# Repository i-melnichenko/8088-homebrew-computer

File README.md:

# 8088 Homebrew Computer

An open-source modular computer built around the Intel 8088 CPU, using
through-hole DIP components and a custom expansion architecture. Development
proceeds incrementally from a minimal working system toward additional hardware
and software capabilities.

## Mainboard Rev. 2.0

| Front | Left-side assembly view |
| --- | --- |
|  |  |

## Firmware and host tools

The repository includes a [32 KiB ROM BIOS](firmware/8088-mainboard/README.md),
[boardctl](tools/boardctl/README.md), and two supported operating systems:

| Operating system | Build from the repository root | Disk image |
| --- | --- | --- |
| [HOME8088 OS](firmware/8088-mainboard/os/home8088/README.md) | `make -C firmware/8088-mainboard os` | `home8088.img` |
| [Microsoft MS-DOS 2.0](firmware/8088-mainboard/os/msdos/README.md) | `make -C firmware/8088-mainboard msdos` | `msdos20.img` |

BIOS performs POST, offers a 20×4 LCD menu for boot/diagnostics/info, and exposes
PC-style hardware services. Both operating systems boot from FAT12
floppy images served by boardctl over UART. Images are writable by default.
Generated base images live in `firmware/8088-mainboard/build/`; keep persistent
DOS files and saves in working copies under `firmware/8088-mainboard/disks/`.

For example, build and boot HOME8088 OS from the repository root:

```sh
make -C firmware/8088-mainboard bios os BIOS_VERSION=dev-disk
go -C tools/boardctl build -o boardctl ./cmd
tools/boardctl/boardctl -port /dev/cu.usbserial-XXXX info
tools/boardctl/boardctl -port /dev/cu.usbserial-XXXX terminal \
  --disk firmware/8088-mainboard/build/home8088.img --boot
```

Install the built BIOS before booting the OS. HOME8088 applications run with
RUN CITY, RUN TIMER or RUN TERMINAL; MS-DOS starts DOS programs by filename.
BIOS/boardctl do not manage application uploads or resident slots. Normal host operations require
[UART protocol 2.0](docs/uart-protocol.md); EEPROM operations negotiate the
installed upgrade transport separately so an older BIOS can still be updated.
The independent updater lives in `firmware/8088-mainboard/bios/programs/flasher`.

Rev. 2 uses on-board UART at 3F8..3FF, 9600 8N1, optional PIC/PIT, and an optional
20×4 LCD with JP1 bridged (80/81 ports). POST detects installed SRAM chips across
00000..9FFFF; the monitor/updater need one working chip anywhere. OS boot requires
RAM0 and a verified timer, reserving the upper 32 KiB of contiguous RAM for BIOS.
The PC timer runs at about 18.2065 Hz. Both operating systems use BIOS disk,
keyboard, console and time services.

Microsoft MS-DOS uses the original, unmodified Microsoft 2.00 kernel and COMMAND
2.02 with the board's OEM I/O layer. The image includes DEBUG and a DOS example;
`make -C firmware/8088-mainboard msdos-zork` adds Zork I in `msdos20-zork.img`.
Prepare a working copy after building DOS, then boot it through the same BIOS
and boardctl (from the repository root):

```sh
mkdir -p firmware/8088-mainboard/disks
cp -n firmware/8088-mainboard/build/msdos20.img firmware/8088-mainboard/disks/msdos20.img
tools/boardctl/boardctl -port /dev/cu.usbserial-XXXX terminal \
  --disk firmware/8088-mainboard/disks/msdos20.img --boot
```

The supported DOS configuration uses the UART console and writable disk images.
Add `--disk-readonly` to protect an image from guest writes.
See the [DOS guide](firmware/8088-mainboard/os/msdos/README.md) for tested programs
and current hardware and storage limits.

## Architecture

The mainboard is built around an Intel 8088 in minimum mode. It exposes a
20-bit address bus (`A0…A19`) and an 8-bit data bus (`D0…D7`); two 74LS373
latches demultiplex `AD0…AD7`, and a 74LS245 buffers the data bus.

## Memory map

| Address range | Function |
| --- | --- |
| `00000h–9FFFFh` | 640 KiB SRAM (five 128 KiB banks) |
| `A0000h–BFFFFh` | `EXP_MEM_CS5#` expansion-memory window, including the conventional `B8000h` video-memory area; available on both Exp0 and Exp1 |
| `C0000h–DFFFFh` | `EXP_MEM_CS6#` expansion-memory / option-ROM window; available on both Exp0 and Exp1 |
| `E0000h–FFFFFh` | 28C256 boot ROM (32 KiB mirrored in the window) |

## I/O map

| Device | Primary ports | Notes |
| --- | --- | --- |
| 8259A PIC | `20h`, `21h` | Interrupt controller |
| 8254 PIT | `40h–43h` | System timer |
| GM16C550 UART | `3F8h–3FFh` | COM1-compatible; mirrored because decoding is partial |
| `EXP_IO_CS4#` | `80h–9Fh` | Expansion I/O window; available on both Exp0 and Exp1 |
| `EXP_IO_CS5#` | `A0h–BFh` | Expansion I/O window; available on both Exp0 and Exp1 |
| `EXP_IO_CS6#` | `C0h–DFh` | Expansion I/O window; available on both Exp0 and Exp1 |

## UART console

The GM16C550 UART provides a COM1-compatible console at `3F8h–3FFh`. Its
1.8432 MHz crystal supports common serial rates; the current BIOS and
`boardctl` use 9600 8N1.

`J9` is a 3-pin TTL UART header (`GND`, `TXD`, `RXD`). To connect the computer
to a USB host, use an external **CP2102 USB-to-TTL adapter**: connect ground
and cross `TXD` with `RXD`. The CP2102 is powered by USB; do not connect its
power pin to the mainboard through `J9`. Verify that the selected CP2102 board
accepts the mainboard's 5 V TTL `TXD` level. This is not an RS-232 interface;
use a MAX232-compatible level converter before connecting an RS-232 port.

## Interrupts and timer

The 8259A PIC operates as a single 8086/8088-mode master and drives the
processor `INTR` input. The 8254 PIT provides the system tick: its channel 0
receives a 1.1931817 MHz clock from a 74LS74 divider and, when programmed with
a divisor of 65,536 in mode 2, produces an 18.2065 Hz interrupt on `IR0`.

| PIC input | PCB connection |
| --- | --- |
| `IR0` | `PIT_IRQ` from the 8254 system timer |
| `IR1` | `EXP_IRQ1` expansion line |
| `IR2` | `EXP_IRQ2` expansion line |
| `IR3` | `EXP_IRQ3` expansion line |
| `IR4` | `UART_IRQ` from the GM16C550 UART |
| `IR5` | `EXP_IRQ5` expansion line |
| `IR6` | `EXP_IRQ6` expansion line |
| `IR7` | `EXP_IRQ7` expansion line |

Each PIC request input has a 10 kΩ pull-down, keeping it inactive when no
device drives the line. Firmware must initialize the PIC and PIT before
enabling interrupts.

## Expansion modules

The mechanical and electrical contract for daughterboards is defined in the
[Expansion Module Standard Rev.2](docs/expansion-module-standard.md).

| Module | Purpose | Documentation |
| --- | --- | --- |
| Display Module | HD44780-compatible character LCD interface | [Configuration and BOM](docs/display-module.md) |
| Smart I/O Module | ESP32-based smart I/O, TFT, and SD interface | [Configuration and BOM](docs/smart-io-module.md) |

## Bill of materials

The table below is derived from [`hardware/kicad`](hardware/kicad) for Rev. 2.0.
It includes both through-hole and SMD components.

| Designators | Qty. | Part / value | Footprint / notes |
| --- | ---: | --- | --- |
| U1 | 1 | Intel 8088, minimum mode | DIP-40, 15.24 mm socket footprint |
| U2, U3 | 2 | 74LS373 | DIP-20, 7.62 mm socket footprint |
| U4 | 1 | 74LS245 | DIP-20, 7.62 mm socket footprint |
| U5 | 1 | 8284 clock generator / driver | DIP-18, 7.62 mm socket footprint |
| U6, U7 | 2 | 74LS138 | DIP-16, 7.62 mm socket footprint |
| U8 | 1 | 28C256 EEPROM | DIP-28 socket footprint; 3M 228-1277-00-0602J |
| U9–U13 | 5 | AS6C1008-55PCN SRAM | DIP-32, 15.24 mm socket footprint |
| U14 | 1 | GM16C550 UART | DIP-40, 15.24 mm socket footprint |
| U15 | 1 | 8259A-2 programmable interrupt controller | DIP-28, 15.24 mm socket footprint |
| U16 | 1 | 8254 programmable interval timer | DIP-24, 15.24 mm socket footprint |
| U17 | 1 | 74LS74 | DIP-14, 7.62 mm socket footprint |
| Q1 | 1 | NDP6020P P-channel MOSFET | TO-220-3, horizontal tab-down |
| Y1 | 1 | 14.31818 MHz crystal | HC-49/U, vertical |
| Y2 | 1 | 1.8432 MHz crystal | HC-49/U, vertical |
| R1–R3, R5–R7, R9–R10, R12, R15–R18, R21–R28 | 21 | 10 kΩ | 0805 SMD |
| R8, R19 | 2 | 1 kΩ | 0805 SMD |
| R11, R20 | 2 | 2 kΩ | 0805 SMD |
| R4 | 1 | 680 Ω | 0805 SMD |
| R13 | 1 | 1 MΩ | 0805 SMD |
| R14 | 1 | 1.5 kΩ | 0805 SMD |
| R29–R44 | 16 | 33 Ω | 0805 SMD; series isolation of the `D0…D7` branches for Exp0 and Exp1 |
| C1–C4, C6–C14, C18–C21 | 17 | 100 nF ceramic | 0805 SMD |
| C5 | 1 | 10 µF electrolytic | Radial, 1.50 mm pitch |
| C15 | 1 | 220 µF electrolytic | Radial, 2.00 mm pitch |
| C16 | 1 | 22 pF ceramic | 0805 SMD |
| C17 | 1 | 47 pF ceramic | 0805 SMD |
| D1 | 1 | Reset LED | 0805 SMD |
| D2 | 1 | Power LED | 0805 SMD |
| SW1 | 1 | 3-position DIP switch | SPST ×3, 2.54 mm pitch |
| SW2 | 1 | Reset pushbutton | 6 mm THT tactile switch |
| J1 | 1 | 10-pin connector | 1×10 pin header, 2.54 mm pitch |
| J2 | 1 | External reset connector | 1×2 pin header, 2.54 mm pitch |
| J3 | 1 | External clock connector | 1×2 pin header, 2.54 mm pitch |
| J4, J6 | 2 | Expansion connectors (Exp0-A, Exp1-A) | 2×20 pin socket, 2.54 mm pitch |
| J5, J7 | 2 | Expansion connectors (Exp0-B, Exp1-B) | 2×10 pin socket, 2.54 mm pitch |
| J8 | 1 | 5 V power input | 2-pin Phoenix MKDS-1,5, 5.08 mm pitch |
| J9 | 1 | CP2102 module connector | 1×3 pin header, 2.54 mm pitch |
| J10, J11 | 2 | 4-pin auxiliary connectors | 1×4 pin header, 2.54 mm pitch |

For ICs, sockets are recommended; the PCB footprints already provide for them.

## Links

- [DIY EEPROM Programmer](https://github.com/erikvanzijst/eeprom)

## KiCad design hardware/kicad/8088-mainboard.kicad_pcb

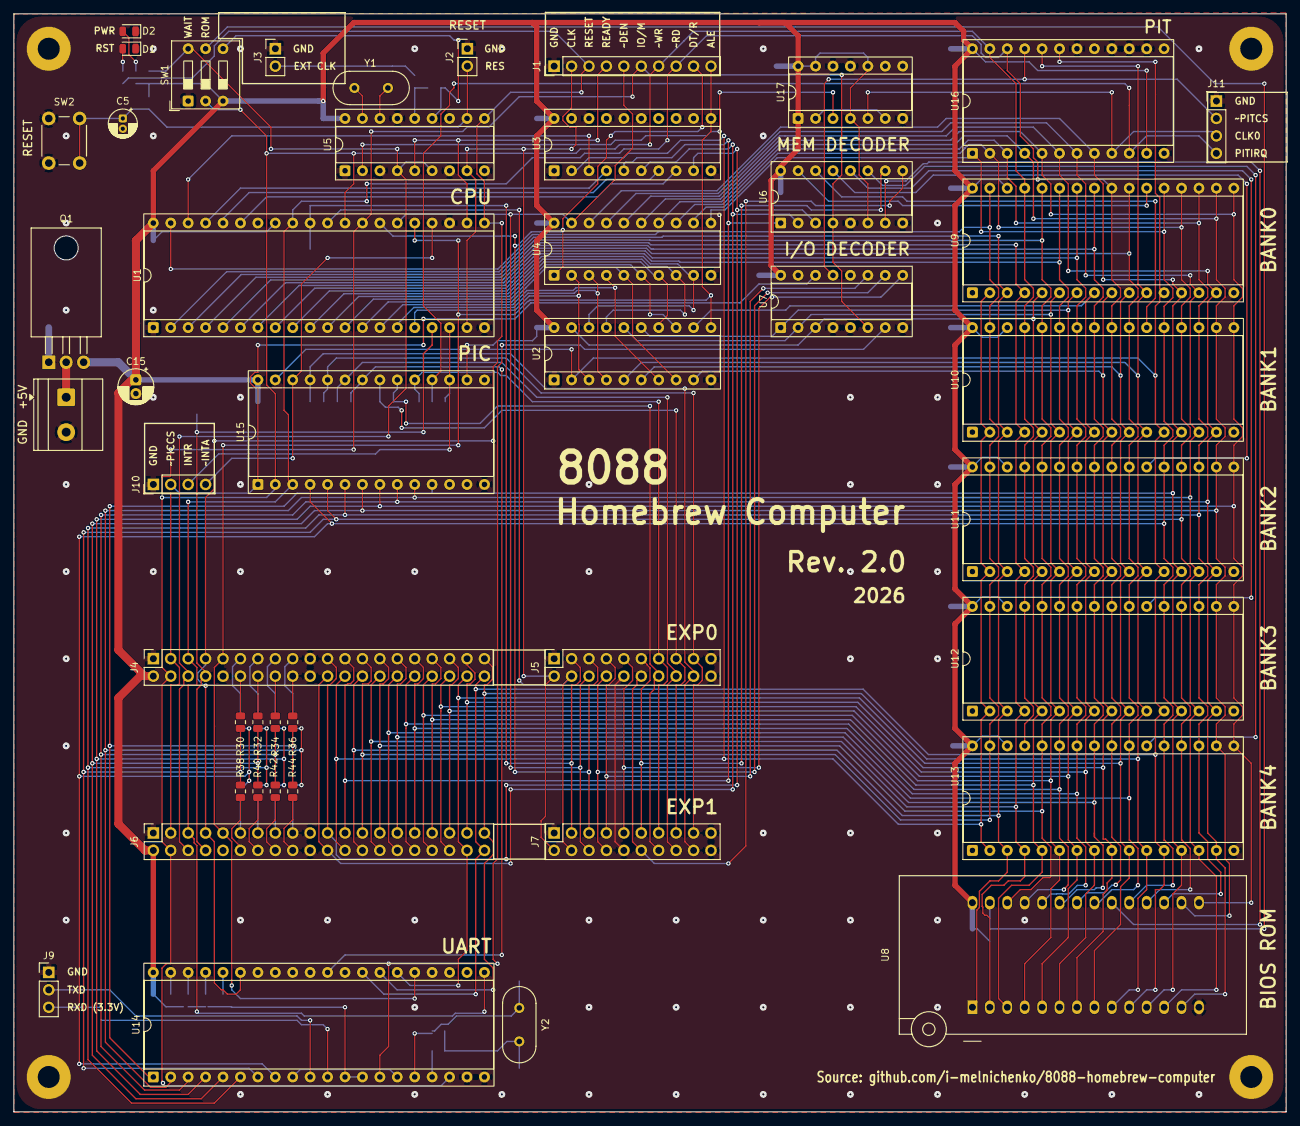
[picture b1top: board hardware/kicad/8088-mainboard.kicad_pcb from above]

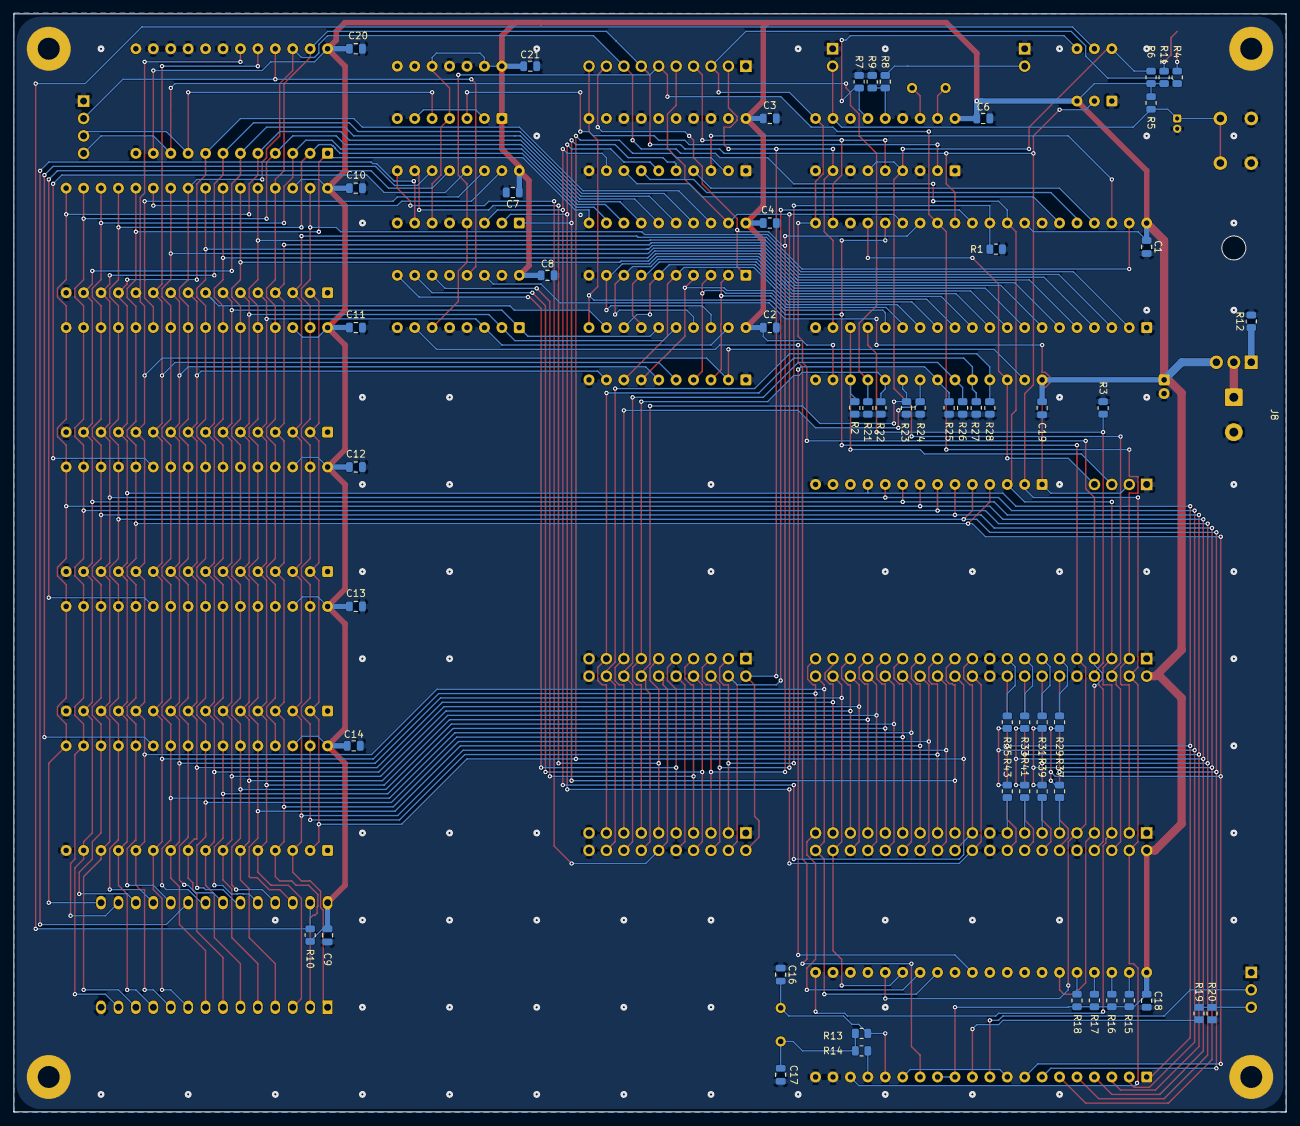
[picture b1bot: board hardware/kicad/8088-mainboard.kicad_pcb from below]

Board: 2 copper layers, 185.4 x 160.0 mm, 104 parts (55 on the bottom side), 120 nets.

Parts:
C1, C2, C3, C4, C7, C8, C9, C10, C11, C12, C13, C14, C18, C19, C20, C21: 100nF; C_0805_2012Metric
C5: 10 uF; CP_Radial_D4.0mm_P1.50mm
C6: 100 nF; C_0805_2012Metric
C15: 220 uF; CP_Radial_D5.0mm_P2.00mm
C16: 22pF; C_0805_2012Metric
C17: 47pF; C_0805_2012Metric
D1: RST LED; LED_0805_2012Metric
D2: PWR LED; LED_0805_2012Metric
H1, H2, H3, H4: MountingHole_Pad; MountingHole_3.2mm_M3_Pad
J1: Conn_01x10; PinHeader_1x10_P2.54mm_Vertical
J2: Ext Res; PinHeader_1x02_P2.54mm_Vertical
J3: Ext CLK; PinHeader_1x02_P2.54mm_Vertical
J4: EXP_0_A; PinSocket_2x20_P2.54mm_Vertical
J5: EXP_0_B; PinSocket_2x10_P2.54mm_Vertical
J6: EXP_1_A; PinSocket_2x20_P2.54mm_Vertical
J7: EXP_1_B; PinSocket_2x10_P2.54mm_Vertical
J8: POWER 5v; TerminalBlock_Phoenix_MKDS-1,5-2-5.08_1x02_P5.08mm_Horizont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
J9: CP2102 Module; PinHeader_1x03_P2.54mm_Vertical
J10, J11: Conn_01x04; PinHeader_1x04_P2.54mm_Vertical
Q1: NDP6020P; TO-220-3_Horizontal_TabDown
R1, R2, R3, R5, R6, R7, R9, R10, R12, R15, R16, R17, R18, R21, R22, R23, R24, R25, R26, R27, R28: 10k; R_0805_2012Metric
R4: 680; R_0805_2012Metric
R8, R19: 1k; R_0805_2012Metric
R11: 2k; R_0805_2012Metric
R13: 1M; R_0805_2012Metric
R14: 1.5k; R_0805_2012Metric
R20: 2K; R_0805_2012Metric
R29, R30, R31, R32, R33, R34, R35, R36, R37, R38, R39, R40, R41, R42, R43, R44: 33; R_0805_2012Metric
SW1: SW_DIP_x03; SW_DIP_SPSTx03_Slide_9.78x9.8mm_W7.62mm_P2.54mm
SW2: Reset; SW_PUSH_6mm
U1: 8088_Min_Mode; DIP-40_W15.24mm_Socket
U2, U3: 74LS373; DIP-20_W7.62mm_Socket
U4: 74LS245; DIP-20_W7.62mm_Socket
U5: 8284; DIP-18_W7.62mm_Socket
U6, U7: 74LS138; DIP-16_W7.62mm_Socket
U8: 28C256; DIP_Socket-28_W11.9mm_W12.7mm_W15.24mm_W17.78mm_W18.5mm_3M_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
U9, U10, U11, U12, U13: AS6C1008-55PCN; DIP-32_W15.24mm_Socket
U14: GM16C550; DIP-40_W15.24mm_Socket
U15: 8259A-2; DIP-28_W15.24mm_Socket
U16: 8254; DIP-24_W15.24mm_Socket
U17: 74LS74; DIP-14_W7.62mm_Socket
Y1: 14.31818 MHz; Crystal_HC49-U_Vertical
Y2: 1.8432 MHz; Crystal_HC49-U_Vertical

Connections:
/A0: J4.40, J6.40, U2.2 (O0), U8.10 (A0), U9.12 (A0), U10.12 (A0), U11.12 (A0), U12.12 (A0), U13.12 (A0), U14.28 (A0), U15.27 (A0), U16.19 (A0)
/A1: J4.39, J6.39, U2.5 (O1), U8.9 (A1), U9.11 (A1), U10.11 (A1), U11.11 (A1), U12.11 (A1), U13.11 (A1), U14.27 (A1), U16.20 (A1)
/A2: J4.38, J6.38, U2.6 (O2), U8.8 (A2), U9.10 (A2), U10.10 (A2), U11.10 (A2), U12.10 (A2), U13.10 (A2), U14.26 (A2)
/A3: J4.37, J6.37, U2.9 (O3), U8.7 (A3), U9.9 (A3), U10.9 (A3), U11.9 (A3), U12.9 (A3), U13.9 (A3)
/A4: J4.36, J6.36, U2.12 (O4), U8.6 (A4), U9.8 (A4), U10.8 (A4), U11.8 (A4), U12.8 (A4), U13.8 (A4)
/A5: J4.35, J6.35, U2.15 (O5), U7.1 (A0), U8.5 (A5), U9.7 (A5), U10.7 (A5), U11.7 (A5), U12.7 (A5), U13.7 (A5)
/A6: J4.34, J6.34, U2.16 (O6), U7.2 (A1), U8.4 (A6), U9.6 (A6), U10.6 (A6), U11.6 (A6), U12.6 (A6), U13.6 (A6)
/A7: J4.33, J6.33, U2.19 (O7), U7.3 (A2), U8.3 (A7), U9.5 (A7), U10.5 (A7), U11.5 (A7), U12.5 (A7), U13.5 (A7)
/A8: J4.32, J6.32, U1.8 (A8), U8.25 (A8), U9.27 (A8), U10.27 (A8), U11.27 (A8), U12.27 (A8), U13.27 (A8)
/A9: J4.31, J6.31, U1.7 (A9), U8.24 (A9), U9.26 (A9), U10.26 (A9), U11.26 (A9), U12.26 (A9), U13.26 (A9)
/A10: J4.30, J6.30, U1.6 (A10), U8.21 (A10), U9.23 (A10), U10.23 (A10), U11.23 (A10), U12.23 (A10), U13.23 (A10)
/A11: J4.29, J6.29, U1.5 (A11), U8.23 (A11), U9.25 (A11), U10.25 (A11), U11.25 (A11), U12.25 (A11), U13.25 (A11)
/A12: J4.28, J6.28, U1.4 (A12), U8.2 (A12), U9.4 (A12), U10.4 (A12), U11.4 (A12), U12.4 (A12), U13.4 (A12)
/A13: J4.27, J6.27, U1.3 (A13), U8.26 (A13), U9.28 (A13), U10.28 (A13), U11.28 (A13), U12.28 (A13), U13.28 (A13)
/A14: J4.26, J6.26, U1.2 (A14), U8.1 (A14), U9.3 (A14), U10.3 (A14), U11.3 (A14), U12.3 (A14), U13.3 (A14)
/A15: J4.25, J6.25, U1.39 (A15), U9.31 (A15), U10.31 (A15), U11.31 (A15), U12.31 (A15), U13.31 (A15)
/A16: J4.24, J6.24, U3.2 (O0), U9.2 (A16), U10.2 (A16), U11.2 (A16), U12.2 (A16), U13.2 (A16)
/A17: J4.23, J6.23, U3.5 (O1), U6.1 (A0)
/A18: J4.22, J6.22, U3.6 (O2), U6.2 (A1)
/A19: J4.21, J6.21, U3.9 (O3), U6.3 (A2)
/ALE: J1.10, J4.9, J6.9, U1.25 (ALE), U2.11 (LE), U3.11 (LE), U14.25 (~ADS)
/CLK: J1.2, J5.2, J7.2, U1.19 (CLK), U5.8 (CLK)
/CLOCK/RES: C5.1, J2.2, R5.2, SW2.1, U5.11 (~RES)
/CLOCK_EFI_SW: R7.1, SW1.4, U5.13 (F/~C)
/CPU/AD0: U1.16 (AD0), U2.3 (D0), U4.2 (A0)
/CPU/AD1: U1.15 (AD1), U2.4 (D1), U4.3 (A1)
/CPU/AD2: U1.14 (AD2), U2.7 (D2), U4.4 (A2)
/CPU/AD3: U1.13 (AD3), U2.8 (D3), U4.5 (A3)
/CPU/AD4: U1.12 (AD4), U2.13 (D4), U4.6 (A4)
/CPU/AD5: U1.11 (AD5), U2.14 (D5), U4.7 (A5)
/CPU/AD6: U1.10 (AD6), U2.17 (D6), U4.8 (A6)
/CPU/AD7: U1.9 (AD7), U2.18 (D7), U4.9 (A7)
/CPU/AD16: U1.38 (A16/S3), U3.3 (D0)
/CPU/AD17: U1.37 (A17/S4), U3.4 (D1)
/CPU/AD18: U1.36 (A18/S5), U3.7 (D2)
/CPU/AD19: U1.35 (A19/S6), U3.8 (D3)
/D0: R36.2, R44.2, U4.18 (B0), U8.11 (D0), U9.13 (DQ0), U10.13 (DQ0), U11.13 (DQ0), U12.13 (DQ0), U13.13 (DQ0), U14.1 (D0), U15.11 (D0), U16.8 (D0)
/D1: R35.2, R43.2, U4.17 (B1), U8.12 (D1), U9.14 (DQ1), U10.14 (DQ1), U11.14 (DQ1), U12.14 (DQ1), U13.14 (DQ1), U14.2 (D1), U15.10 (D1), U16.7 (D1)
/D2: R34.2, R42.2, U4.16 (B2), U8.13 (D2), U9.15 (DQ2), U10.15 (DQ2), U11.15 (DQ2), U12.15 (DQ2), U13.15 (DQ2), U14.3 (D2), U15.9 (D2), U16.6 (D2)
/D3: R33.2, R41.2, U4.15 (B3), U8.15 (D3), U9.17 (DQ3), U10.17 (DQ3), U11.17 (DQ3), U12.17 (DQ3), U13.17 (DQ3), U14.4 (D3), U15.8 (D3), U16.5 (D3)
/D4: R32.2, R40.2, U4.14 (B4), U8.16 (D4), U9.18 (DQ4), U10.18 (DQ4), U11.18 (DQ4), U12.18 (DQ4), U13.18 (DQ4), U14.5 (D4), U15.7 (D4), U16.4 (D4)
/D5: R31.2, R39.2, U4.13 (B5), U8.17 (D5), U9.19 (DQ5), U10.19 (DQ5), U11.19 (DQ5), U12.19 (DQ5), U13.19 (DQ5), U14.6 (D5), U15.6 (D5), U16.3 (D5)
/D6: R30.2, R38.2, U4.12 (B6), U8.18 (D6), U9.20 (DQ6), U10.20 (DQ6), U11.20 (DQ6), U12.20 (DQ6), U13.20 (DQ6), U14.7 (D6), U15.5 (D6), U16.2 (D6)
/D7: R29.2, R37.2, U4.11 (B7), U8.19 (D7), U9.21 (DQ7), U10.21 (DQ7), U11.21 (DQ7), U12.21 (DQ7), U13.21 (DQ7), U14.8 (D7), U15.4 (D7), U16.1 (D7)
/DEN: J1.5, J5.6, J7.6, U1.26 (DEN), U4.19 (CE)
/DT_R: J1.9, J5.5, J7.5, U1.27 (DT/~R), U4.1 (A->B)
/EXPANSION_CONNECTOR/EXP_IO_CS4: J5.7, J7.7, U7.11 (O4)
/EXPANSION_CONNECTOR/EXP_IO_CS5: J5.8, J7.8, U7.10 (O5)
/EXPANSION_CONNECTOR/EXP_IO_CS6: J5.9, J7.9, U7.9 (O6)
/EXP_IRQ1: J5.13, J7.13, R22.1, U15.19 (IR1)
/EXP_IRQ2: J5.14, J7.14, R23.1, U15.20 (IR2)
/EXP_IRQ3: J5.15, J7.15, R24.1, U15.21 (IR3)
/EXP_IRQ5: J5.16, J7.16, R26.1, U15.23 (IR5)
/EXP_IRQ6: J5.17, J7.17, R27.1, U15.24 (IR6)
/EXP_IRQ7: J5.18, J7.18, R28.1, U15.25 (IR7)
/EXP_MEM_CS5: J5.11, J7.11, U6.10 (O5)
/EXP_MEM_CS6: J5.12, J7.12, U6.9 (O6)
/HLDA: J5.4, J7.4, U1.30 (HLDA)
/HOLD: J5.3, J7.3, R1.1, U1.31 (HOLD)
/INTA: J10.4, U1.24 (~INTA), U15.26 (~INTA)
/INTR: J10.3, R2.1, U1.18 (INTR), U15.17 (INT)
/IOM: J1.6, J4.3, J6.3, U1.28 (IO/~M), U6.4 (E1), U7.6 (E3)
/IO_DECODER/IO_PIT_CS: J11.2, U7.13 (O2), U16.21 (~CS)
/IO_PIC_CS: J10.2, U7.14 (O1), U15.1 (~CS)
/IO_UART_CS: U7.7 (O7), U14.14 (~CS2)
/MEM_DECODER/RAM_BANK0_CS: U6.15 (O0), U9.22 (~CS1/~CE1)
/MEM_DECODER/RAM_BANK1_CS: U6.14 (O1), U10.22 (~CS1/~CE1)
/MEM_DECODER/RAM_BANK2_CS: U6.13 (O2), U11.22 (~CS1/~CE1)
/MEM_DECODER/RAM_BANK3_CS: U6.12 (O3), U12.22 (~CS1/~CE1)
/MEM_DECODER/RAM_BANK4_CS: U6.11 (O4), U13.22 (~CS1/~CE1)
/MEM_DECODER/ROM_CS: U6.7 (O7), U8.20 (~CS)
/NMI: J4.8, J6.8, R3.1, U1.17 (NMI)
/PCLK: U5.2 (PCLK), U17.3 (C)
/PIT/CLK0: J11.3, U16.9 (CLK0), U17.5 (Q)
/PIT_IRQ: J11.4, R21.1, U15.18 (IR0), U16.10 (OUT0)
/RD: J1.8, J4.5, J6.5, U1.32 (~RD), U8.22 (~OE), U9.24 (~OE), U10.24 (~OE), U11.24 (~OE), U12.24 (~OE), U13.24 (~OE), U14.21 (~RD), U15.3 (~RD), U16.22 (~RD)
/RDY: J4.6, J6.6, R6.2, SW1.6, U5.4 (RDY1), U5.6 (RDY2)
/READY: J1.4, U1.22 (READY), U5.5 (READY)
/RESET: J1.3, J4.7, J6.7, R4.1, U1.21 (RESET), U5.10 (RESET), U14.35 (MR)
/ROM_WE_SW: R10.2, SW1.5, U8.27 (~WE)
/UART/RXI: J9.3, R19.2, R20.2
/UART/TXD: J9.2, U14.10 (SIN)
/UART_IRQ: R25.1, U14.30 (INTR), U15.22 (IR4)
/WR: J1.7, J4.4, J6.4, SW1.2, U1.29 (~WR), U9.29 (~WE), U10.29 (~WE), U11.29 (~WE), U12.29 (~WE), U13.29 (~WE), U14.18 (~WR), U15.2 (~WR), U16.23 (~WR)
GND: C1.2, C2.2, C3.2, C4.2, C5.2, C6.2, C7.2, C8.2, C9.2, C10.2, C11.2, C12.2, C13.2, C14.2, C15.2, C16.1, C17.1, C18.2, C19.2, C20.2, C21.2, D1.1 (K), D2.1 (K), H1.1 (1_1), H2.1 (1_1), H3.1 (1_1), H4.1 (1_1), J1.1, J2.1, J3.1, J4.1, J4.10, J4.19, J4.20, J5.1, J5.10, J5.19, J5.20, J6.1, J6.10, J6.19, J6.20, J7.1, J7.10, J7.19, J7.20, J8.2, J9.1, J10.1, J11.1, R1.2, R2.2, R3.2, R7.2, R9.2, R12.2, R20.1, R21.2, R22.2, R23.2, R24.2, R25.2, R26.2, R27.2, R28.2, SW1.1, SW2.2, U1.1 (GND), U1.20 (GND), U1.23 (~TEST), U2.1 (OE), U2.10 (GND), U3.1 (OE), U3.10 (GND), U3.13 (D4), U3.14 (D5), U3.17 (D6), U3.18 (D7), U4.10 (GND), U5.1 (CSYNC), U5.3 (~AEN1), U5.7 (~AEN2), U5.9 (GND), U5.15 (~ASYNC), U6.5 (E2), U6.8 (GND), U7.4 (E1), U7.5 (E2), U7.8 (GND), U8.14 (GND), U9.16 (GND), U10.16 (GND), U11.16 (GND), U12.16 (GND), U13.16 (GND), U14.19 (WR), U14.20 (GND), U14.22 (RD), U15.14 (GND), U16.12 (GND), U16.14 (G1), U16.15 (CLK1), U16.16 (G2), U16.18 (CLK2), U17.7 (GND), U17.11 (C), U17.12 (D)
unnamed: C17.2, R13.1, R14.1, Y2.1
unnamed: D1.2 (A), R4.2
unnamed: D2.2 (A), R11.2
unnamed: J3.2, R8.2
unnamed: J4.11, R29.1
unnamed: J4.12, R30.1
unnamed: J4.13, R31.1
unnamed: J4.14, R32.1
unnamed: J4.15, R33.1
unnamed: J4.16, R34.1
unnamed: J4.17, R35.1
unnamed: J4.18, R36.1
unnamed: J6.11, R37.1
unnamed: J6.12, R38.1
unnamed: J6.13, R39.1
unnamed: J6.14, R40.1
unnamed: J6.15, R41.1
unnamed: J6.16, R42.1
unnamed: J6.17, R43.1
unnamed: J6.18, R44.1
unnamed: J8.1, Q1.2 (D)
unnamed: Q1.1 (G), R12.1
unnamed: R8.1, R9.1, U5.14 (EFI)
unnamed: U5.17 (X1), Y1.2
unnamed: U5.16 (X2), Y1.1
unnamed: U14.9 (RCLK), U14.15 (~BAUDOUT)
unnamed: R19.1, U14.11 (SOUT)
unnamed: C16.2, R13.2, U14.16 (XIN), Y2.2
unnamed: R14.2, U14.17 (XOUT)
unnamed: R18.2, U14.36 (~CTS)
unnamed: R16.2, U14.38 (~DCD)
unnamed: R17.2, U14.37 (~DSR)
unnamed: R15.2, U14.39 (~RI)
unnamed: U17.2 (D), U17.6 (~Q)
VCC: C1.1, C2.1, C3.1, C4.1, C6.1, C7.1, C8.1, C9.1, C10.1, C11.1, C12.1, C13.1, C14.1, C15.1, C18.1, C19.1, C20.1, C21.1, J4.2, J6.2, Q1.3 (S), R5.1, R6.1, R10.1, R11.1, R15.1, R16.1, R17.1, R18.1, SW1.3, U1.33 (MN/~MX), U1.40 (VCC), U2.20 (VCC), U3.20 (VCC), U4.20 (VCC), U5.18 (VCC), U6.6 (E3), U6.16 (VCC), U7.16 (VCC), U8.28 (VCC), U9.30 (CS2/CE2), U9.32 (VCC), U10.30 (CS2/CE2), U10.32 (VCC), U11.30 (CS2/CE2), U11.32 (VCC), U12.30 (CS2/CE2), U12.32 (VCC), U13.30 (CS2/CE2), U13.32 (VCC), U14.12 (CS0), U14.13 (CS1), U14.40 (VCC), U15.16 (~SP/~EN), U15.28 (VCC), U16.11 (G0), U16.24 (VCC), U17.1 (~R), U17.4 (~S), U17.10 (~S), U17.13 (~R), U17.14 (VCC)

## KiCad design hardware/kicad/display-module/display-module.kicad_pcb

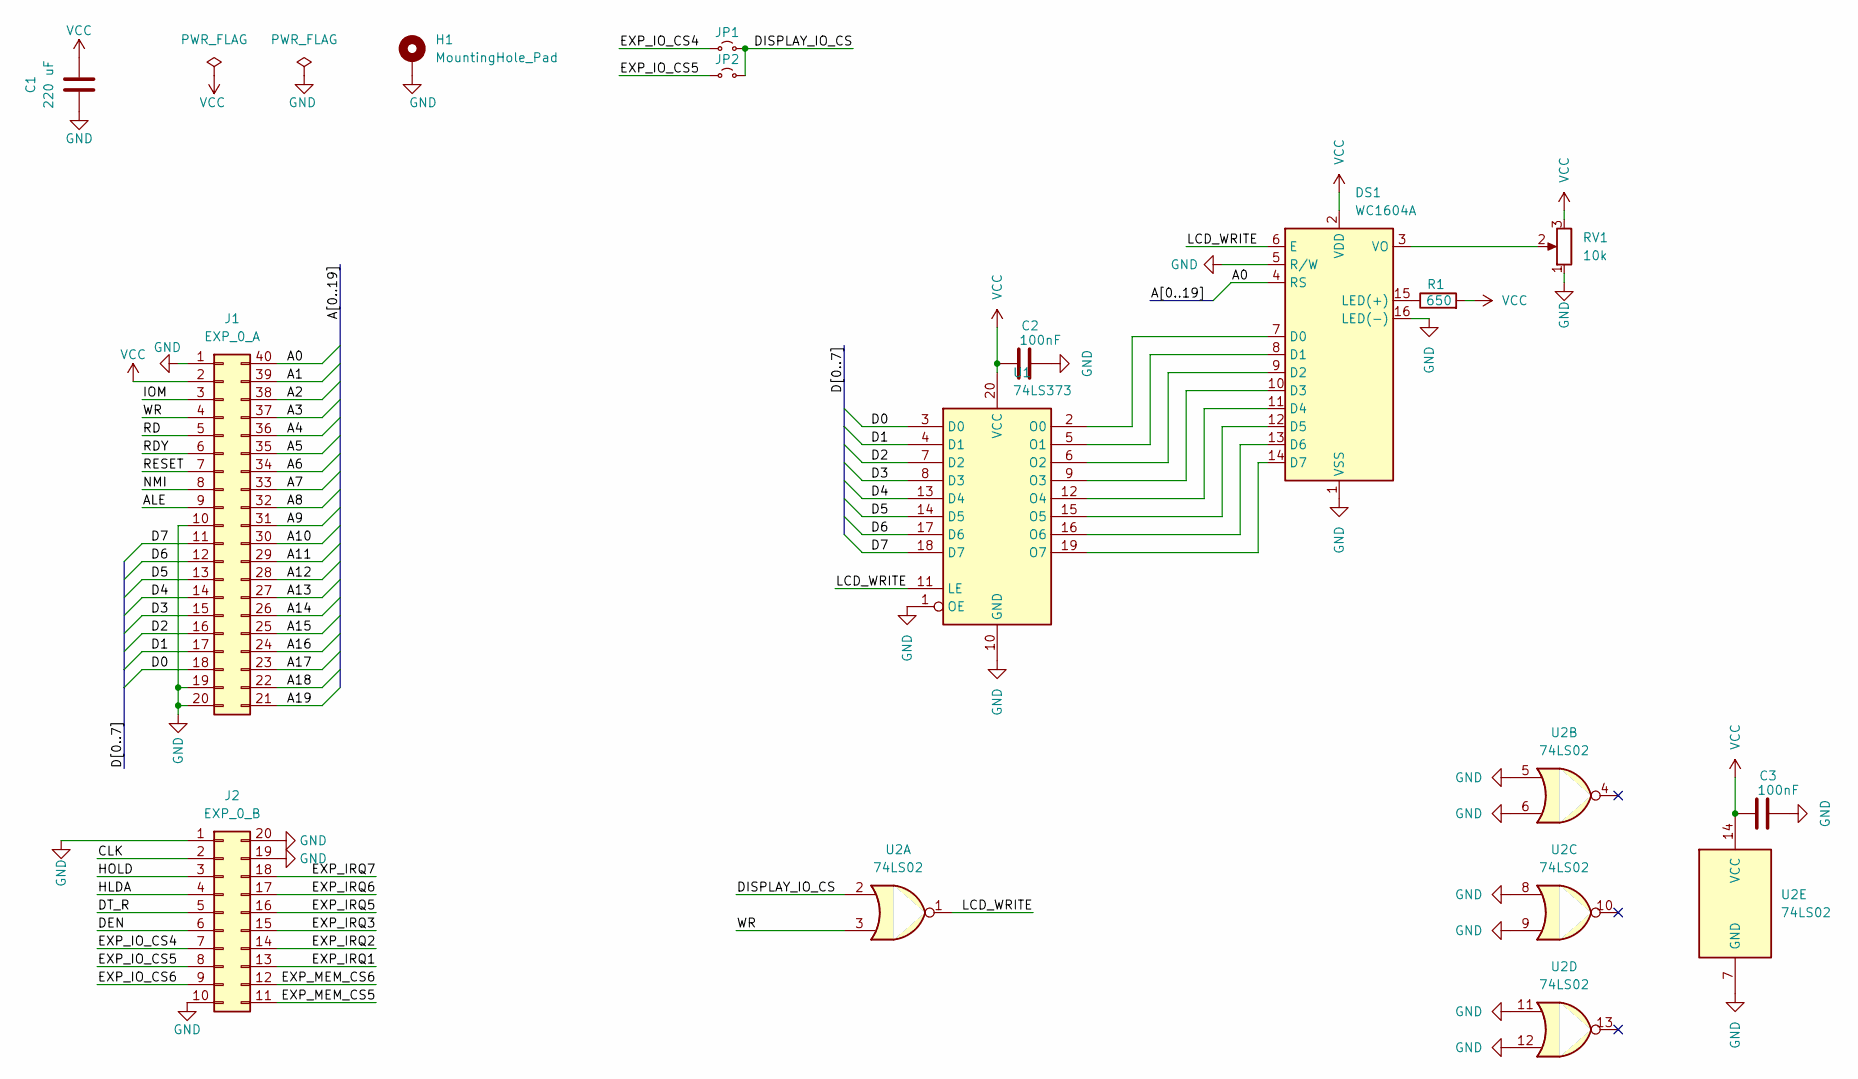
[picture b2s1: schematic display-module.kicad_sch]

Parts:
C1: 220 uF; CP_Radial_D5.0mm_P2.00mm
C2, C3: 100nF; C_Disc_D5.0mm_W2.5mm_P5.00mm
DS1: WC1604A; PinHeader_1x16_P2.54mm_Horizontal
H1: MountingHole_Pad; MountingHole_3.2mm_M3_Pad
J1: EXP_0_A; PinHeader_2x20_P2.54mm_Horizontal
J2: EXP_0_B; PinHeader_2x10_P2.54mm_Horizontal
JP1, JP2: Jumper_2_Small_Open; SolderJumper-2_P1.3mm_Open_Pad1.0x1.5mm
R1: 650; R_Axial_DIN0207_L6.3mm_D2.5mm_P7.62mm_Horizontal
RV1: 10k; Potentiometer_Runtron_RM-065_Vertical
U1: 74LS373; DIP-20_W7.62mm_Socket
U2: 74LS02; DIP-14_W7.62mm_Socket

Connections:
/A0: DS1.4 (RS), J1.40
/A1: J1.39
/A2: J1.38
/A3: J1.37
/A4: J1.36
/A5: J1.35
/A6: J1.34
/A7: J1.33
/A8: J1.32
/A9: J1.31
/A10: J1.30
/A11: J1.29
/A12: J1.28
/A13: J1.27
/A14: J1.26
/A15: J1.25
/A16: J1.24
/A17: J1.23
/A18: J1.22
/A19: J1.21
/ALE: J1.9
/CLK: J2.2
/D0: J1.18, U1.3 (D0)
/D1: J1.17, U1.4 (D1)
/D2: J1.16, U1.7 (D2)
/D3: J1.15, U1.8 (D3)
/D4: J1.14, U1.13 (D4)
/D5: J1.13, U1.14 (D5)
/D6: J1.12, U1.17 (D6)
/D7: J1.11, U1.18 (D7)
/DEN: J2.6
/DISPLAY_IO_CS: JP1.2 (B), JP2.2 (B), U2.2
/DT_R: J2.5
/EXP_IO_CS4: J2.7, JP1.1 (A)
/EXP_IO_CS5: J2.8, JP2.1 (A)
/EXP_IO_CS6: J2.9
/EXP_IRQ1: J2.13
/EXP_IRQ2: J2.14
/EXP_IRQ3: J2.15
/EXP_IRQ5: J2.16
/EXP_IRQ6: J2.17
/EXP_IRQ7: J2.18
/EXP_MEM_CS5: J2.11
/EXP_MEM_CS6: J2.12
/HLDA: J2.4
/HOLD: J2.3
/IOM: J1.3
/LCD_WRITE: DS1.6 (E), U1.11 (LE), U2.1
/NMI: J1.8
/RD: J1.5
/RDY: J1.6
/RESET: J1.7
/WR: J1.4, U2.3
GND: C1.2, C2.2, C3.2, DS1.1 (VSS), DS1.5 (R/W), DS1.16 (LED(-)), H1.1 (1_1), J1.1, J1.10, J1.19, J1.20, J2.1, J2.10, J2.19, J2.20, RV1.1, U1.1 (OE), U1.10 (GND), U2.5, U2.6, U2.7 (GND), U2.8, U2.9, U2.11, U2.12
unnamed: DS1.7 (D0), U1.2 (O0)
unnamed: DS1.8 (D1), U1.5 (O1)
unnamed: DS1.9 (D2), U1.6 (O2)
unnamed: DS1.10 (D3), U1.9 (O3)
unnamed: DS1.11 (D4), U1.12 (O4)
unnamed: DS1.12 (D5), U1.15 (O5)
unnamed: DS1.13 (D6), U1.16 (O6)
unnamed: DS1.14 (D7), U1.19 (O7)
unnamed: DS1.15 (LED(+)), R1.1
unnamed: DS1.3 (VO), RV1.2
VCC: C1.1, C2.1, C3.1, DS1.2 (VDD), J1.2, R1.2, RV1.3, U1.20 (VCC), U2.14 (VCC)

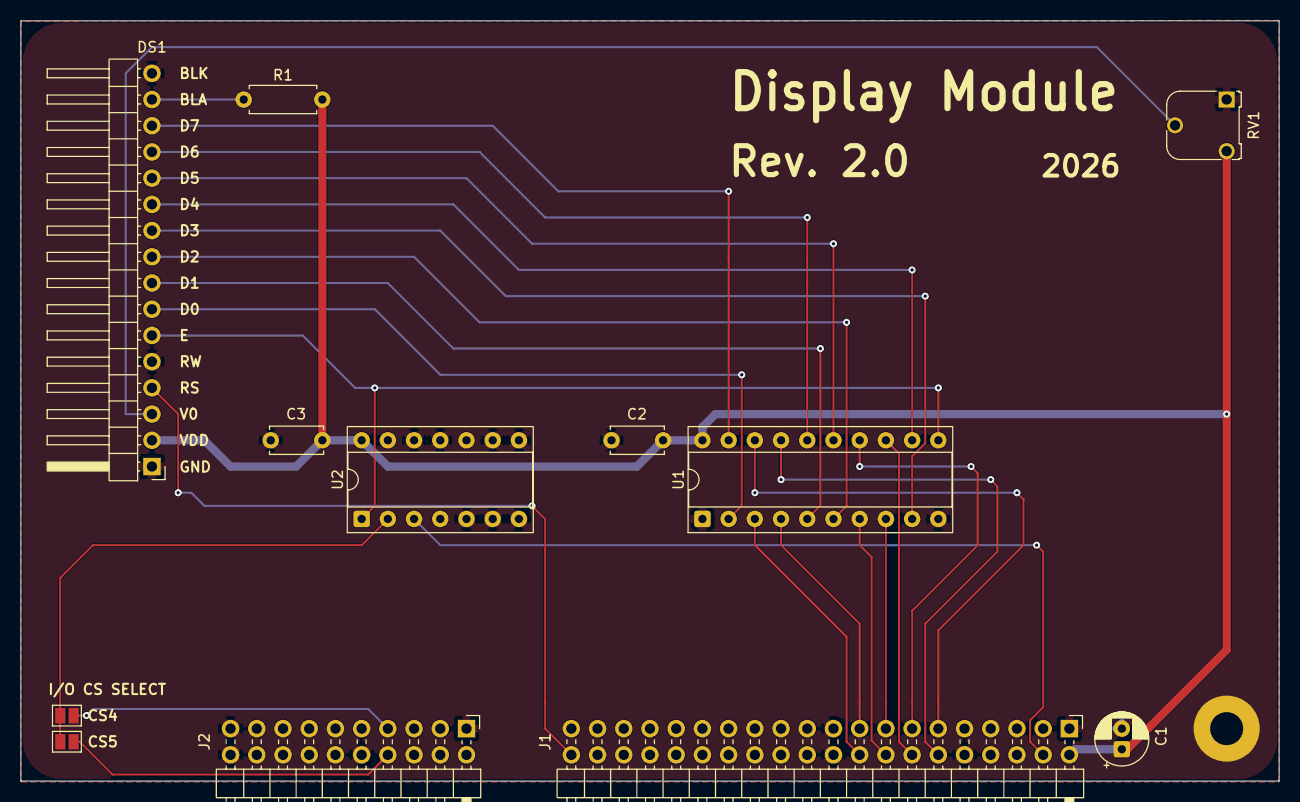
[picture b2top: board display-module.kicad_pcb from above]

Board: 2 copper layers, 121.9 x 73.7 mm, 13 parts (0 on the bottom side), 26 nets.

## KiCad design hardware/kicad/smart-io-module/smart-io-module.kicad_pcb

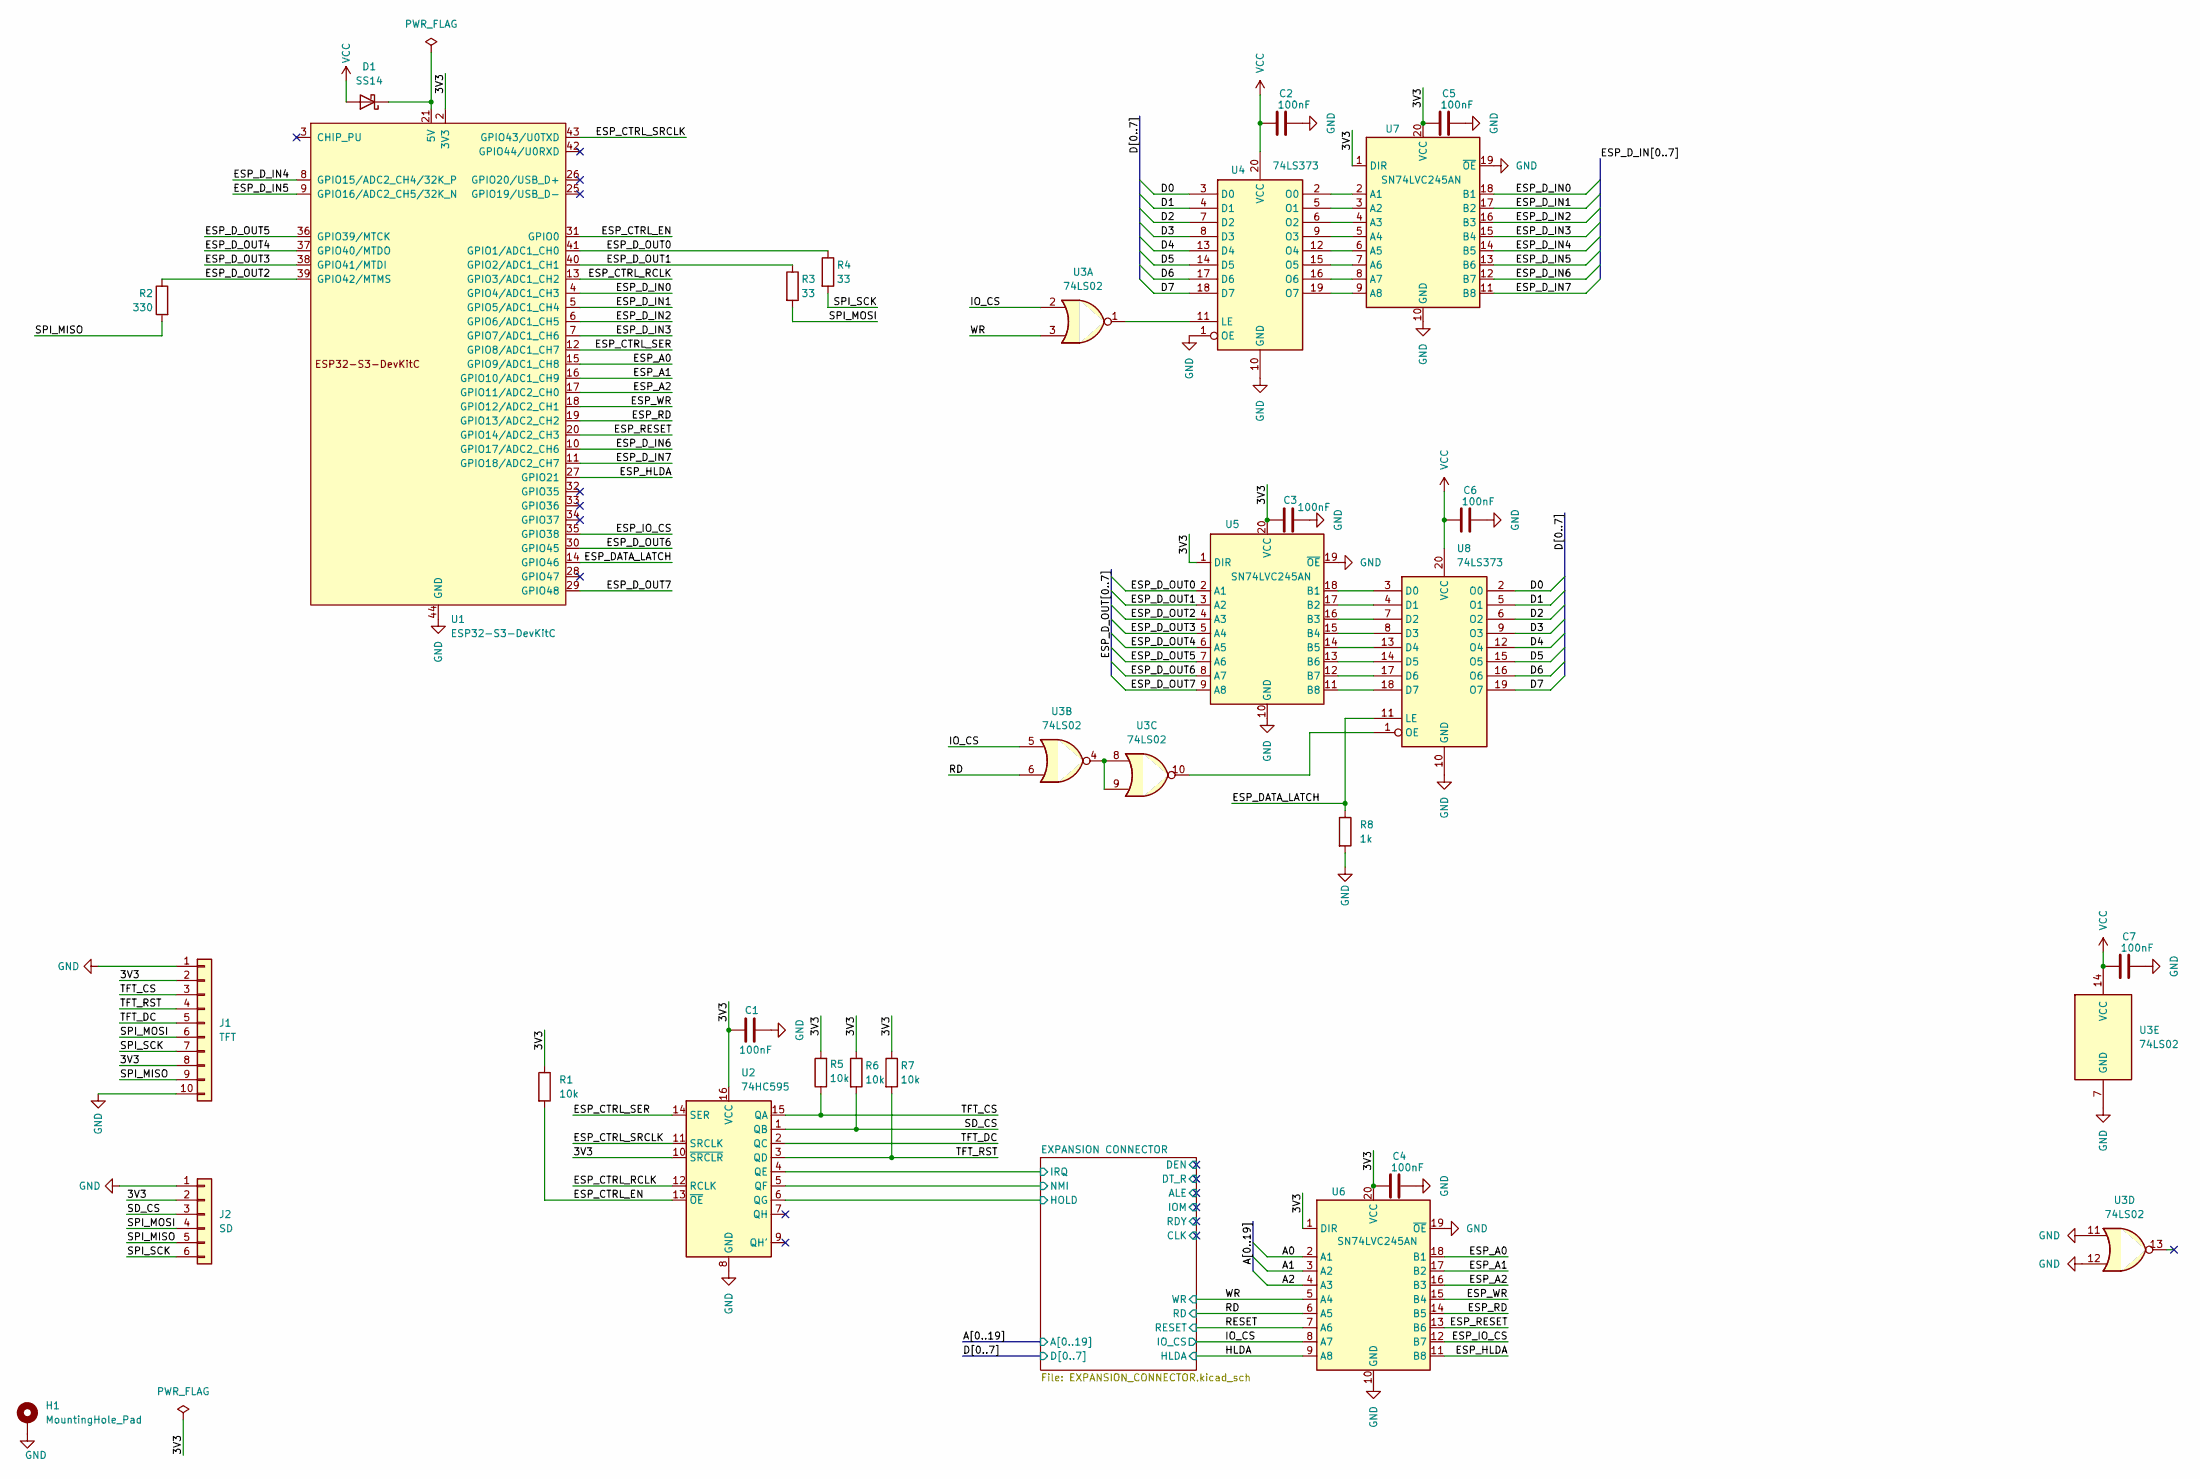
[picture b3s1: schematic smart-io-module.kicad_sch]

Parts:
C1, C2, C3, C4, C5, C6, C7: 100nF; C_0805_2012Metric
D1: SS14; D_SMA
H1: MountingHole_Pad; MountingHole_3.2mm_M3_Pad
J1: TFT; PinHeader_1x10_P2.54mm_Horizontal
J2: SD; PinHeader_1x06_P2.54mm_Horizontal
R1, R5, R6, R7: 10k; R_0805_2012Metric
R2: 330; R_0805_2012Metric
R3, R4: 33; R_0805_2012Metric
R8: 1k; R_0805_2012Metric
U1: ESP32-S3-DevKitC
U2: 74HC595; DIP-16_W7.62mm_Socket
U3: 74LS02; DIP-14_W7.62mm_Socket
U4, U8: 74LS373; DIP-20_W7.62mm_Socket
U5, U6, U7: SN74LVC245AN; DIP-20_W7.62mm_Socket

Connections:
/3V3: C1.1, C3.1, C4.1, C5.1, J1.2, J1.8, J2.2, R1.1, R5.2, R6.1, R7.1, U1.1 (3V3), U1.2 (3V3), U2.10 (~SRCLR), U2.16 (VCC), U5.1 (DIR), U5.20 (VCC), U6.1 (DIR), U6.20 (VCC), U7.1 (DIR), U7.20 (VCC)
/A0: U6.2 (A1); also elsewhere on the board
/A1: U6.3 (A2); also elsewhere on the board
/A2: U6.4 (A3); also elsewhere on the board
/D0: U4.3 (D0), U8.2 (O0); also elsewhere on the board
/D1: U4.4 (D1), U8.5 (O1); also elsewhere on the board
/D2: U4.7 (D2), U8.6 (O2); also elsewhere on the board
/D3: U4.8 (D3), U8.9 (O3); also elsewhere on the board
/D4: U4.13 (D4), U8.12 (O4); also elsewhere on the board
/D5: U4.14 (D5), U8.15 (O5); also elsewhere on the board
/D6: U4.17 (D6), U8.16 (O6); also elsewhere on the board
/D7: U4.18 (D7), U8.19 (O7); also elsewhere on the board
/ESP_A0: U1.15 (GPIO9/ADC1_CH8), U6.18 (B1)
/ESP_A1: U1.16 (GPIO10/ADC1_CH9), U6.17 (B2)
/ESP_A2: U1.17 (GPIO11/ADC2_CH0), U6.16 (B3)
/ESP_CTRL_EN: R1.2, U1.31 (GPIO0), U2.13 (~OE)
/ESP_CTRL_RCLK: U1.13 (GPIO3/ADC1_CH2), U2.12 (RCLK)
/ESP_CTRL_SER: U1.12 (GPIO8/ADC1_CH7), U2.14 (SER)
/ESP_CTRL_SRCLK: U1.43 (GPIO43/U0TXD), U2.11 (SRCLK)
/ESP_DATA_LATCH: R8.1, U1.14 (GPIO46), U8.11 (LE)
/ESP_D_IN0: U1.4 (GPIO4/ADC1_CH3), U7.18 (B1)
/ESP_D_IN1: U1.5 (GPIO5/ADC1_CH4), U7.17 (B2)
/ESP_D_IN2: U1.6 (GPIO6/ADC1_CH5), U7.16 (B3)
/ESP_D_IN3: U1.7 (GPIO7/ADC1_CH6), U7.15 (B4)
/ESP_D_IN4: U1.8 (GPIO15/ADC2_CH4/32K_P), U7.14 (B5)
/ESP_D_IN5: U1.9 (GPIO16/ADC2_CH5/32K_N), U7.13 (B6)
/ESP_D_IN6: U1.10 (GPIO17/ADC2_CH6), U7.12 (B7)
/ESP_D_IN7: U1.11 (GPIO18/ADC2_CH7), U7.11 (B8)
/ESP_D_OUT0: R4.1, U1.41 (GPIO1/ADC1_CH0), U5.2 (A1)
/ESP_D_OUT1: R3.1, U1.40 (GPIO2/ADC1_CH1), U5.3 (A2)
/ESP_D_OUT2: R2.1, U1.39 (GPIO42/MTMS), U5.4 (A3)
/ESP_D_OUT3: U1.38 (GPIO41/MTDI), U5.5 (A4)
/ESP_D_OUT4: U1.37 (GPIO40/MTDO), U5.6 (A5)
/ESP_D_OUT5: U1.36 (GPIO39/MTCK), U5.7 (A6)
/ESP_D_OUT6: U1.30 (GPIO45), U5.8 (A7)
/ESP_D_OUT7: U1.29 (GPIO48), U5.9 (A8)
/ESP_HLDA: U1.27 (GPIO21), U6.11 (B8)
/ESP_IO_CS: U1.35 (GPIO38), U6.12 (B7)
/ESP_RD: U1.19 (GPIO13/ADC2_CH2), U6.14 (B5)
/ESP_RESET: U1.20 (GPIO14/ADC2_CH3), U6.13 (B6)
/ESP_WR: U1.18 (GPIO12/ADC2_CH1), U6.15 (B4)
/EXPANSION CONNECTOR/HOLD: U2.6 (QG); also elsewhere on the board
/EXPANSION CONNECTOR/IRQ: U2.4 (QE); also elsewhere on the board
/EXPANSION CONNECTOR/NMI: U2.5 (QF); also elsewhere on the board
/HLDA: U6.9 (A8); also elsewhere on the board
/IO_CS: U3.2, U3.5, U6.8 (A7); also elsewhere on the board
/RD: U3.6, U6.6 (A5); also elsewhere on the board
/RESET: U6.7 (A6); also elsewhere on the board
/SD_CS: J2.3, R6.2, U2.1 (QB)
/SPI_MISO: J1.9, J2.5, R2.2
/SPI_MOSI: J1.6, J2.4, R3.2
/SPI_SCK: J1.7, J2.6, R4.2
/TFT_CS: J1.3, R5.1, U2.15 (QA)
/TFT_DC: J1.5, U2.2 (QC)
/TFT_RST: J1.4, R7.2, U2.3 (QD)
/WR: U3.3, U6.5 (A4); also elsewhere on the board
GND: C1.2, C2.2, C3.2, C4.2, C5.2, C6.2, C7.2, H1.1 (1_1), J1.1, J1.10, J2.1, R8.2, U1.22 (GND), U1.23 (GND), U1.24 (GND), U1.44 (GND), U2.8 (GND), U3.7 (GND), U3.11, U3.12, U4.1 (OE), U4.10 (GND), U5.10 (GND), U5.19 (~OE), U6.10 (GND), U6.19 (~OE), U7.10 (GND), U7.19 (~OE), U8.10 (GND); also elsewhere on the board
unnamed: D1.1 (K), U1.21 (5V)
unnamed: U3.4, U3.8, U3.9
unnamed: U3.1, U4.11 (LE)
unnamed: U4.2 (O0), U7.2 (A1)
unnamed: U4.5 (O1), U7.3 (A2)
unnamed: U4.6 (O2), U7.4 (A3)
unnamed: U4.9 (O3), U7.5 (A4)
unnamed: U4.12 (O4), U7.6 (A5)
unnamed: U4.15 (O5), U7.7 (A6)
unnamed: U4.16 (O6), U7.8 (A7)
unnamed: U4.19 (O7), U7.9 (A8)
unnamed: U5.18 (B1), U8.3 (D0)
unnamed: U5.17 (B2), U8.4 (D1)
unnamed: U5.16 (B3), U8.7 (D2)
unnamed: U5.15 (B4), U8.8 (D3)
unnamed: U5.14 (B5), U8.13 (D4)
unnamed: U5.13 (B6), U8.14 (D5)
unnamed: U5.12 (B7), U8.17 (D6)
unnamed: U5.11 (B8), U8.18 (D7)
unnamed: U3.10, U8.1 (OE)
VCC: C2.1, C6.1, C7.1, D1.2 (A), U3.14 (VCC), U4.20 (VCC), U8.20 (VCC); also elsewhere on the board
